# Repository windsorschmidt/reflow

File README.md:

# Reflow Oven Controller

_"Yeah man, but it's a **dry** heat!."_ —PFC William L. Hudson

## About

Hardware and firmware sources for a 2-channel reflow (toaster) oven controller.

In spite of great alternatives such as [Controleo3](http://www.whizoo.com/controleo3), I decided to build my own controller for personal use. The design is intended to be simple and self-contained. Comments and pull requests are welcome!

Some pictures of the assembled controller and completed oven retrofit [are online here](https://imgur.com/gallery/L4Zu2G3).

|  |  |

## Hardware Features

- Two triac-controlled power outputs (no external SSRs needed)
- AC line zero-crossing detection for reduced switching noise
- Temperature sensor using MAX31855 K-type thermocouple amplifier
- Compact user interface with OLED display and Cherry MX key-switches
- Data-logging output though USB and serial-to-Bluetooth module
- Tone transducer for audible alerts (e.g. reflow cycle complete)
- Mounts in a dedicated enclosure for simple wiring using IEC connectors
- [Aliens](https://en.wikipedia.org/wiki/Aliens_(film)) film inspired aesthetics

## Firmware Features

- Non-profiling PID routine controls triac outputs to track the active reflow profile
- Reflow profile can be viewed & edited at run-time (currently no ability to save edits)

## References

- [This project](https://www.allaboutcircuits.com/projects/controlling-ac-mains-with-a-microcontroller-for-fun-and-profit) was used as a basis for the triac control and zero-crossing detection circuitry
- [This Reddit user](https://www.reddit.com/user/rich-creamery-butter) provided [Assembly pics](https://imgur.com/a/sCKgO) used as a guide when converting my own oven
- The excellent [u8g2](https://github.com/olikraus/u8g2) library used to render user-interface graphics and text
- [Yusuke Kamiyamane](mailto:p@yusukekamiyamane.com)'s Tempesta Seven font used in the gnuplot script
- [KiCad](http://kicad-pcb.org/) EDA suite used for hardware schematic capture and PCB layout

## Disclaimer

This information is supplied "as is" and without warranties of any kind, express, implied, or statutory including, but not limited to, any implied warranty of merchantability, noninfringement or fitness for a particular purpose and no responsibility is assumed by the author for its use, nor for any infringements of patents or other rights of third parties that may result from its use.

In no event will the author be liable for any loss or damage including without limitation, indirect or consequential loss or damage, or any loss or damage whatsoever arising from or in connection with the use of this information.

## License

[MIT license](LICENSE)

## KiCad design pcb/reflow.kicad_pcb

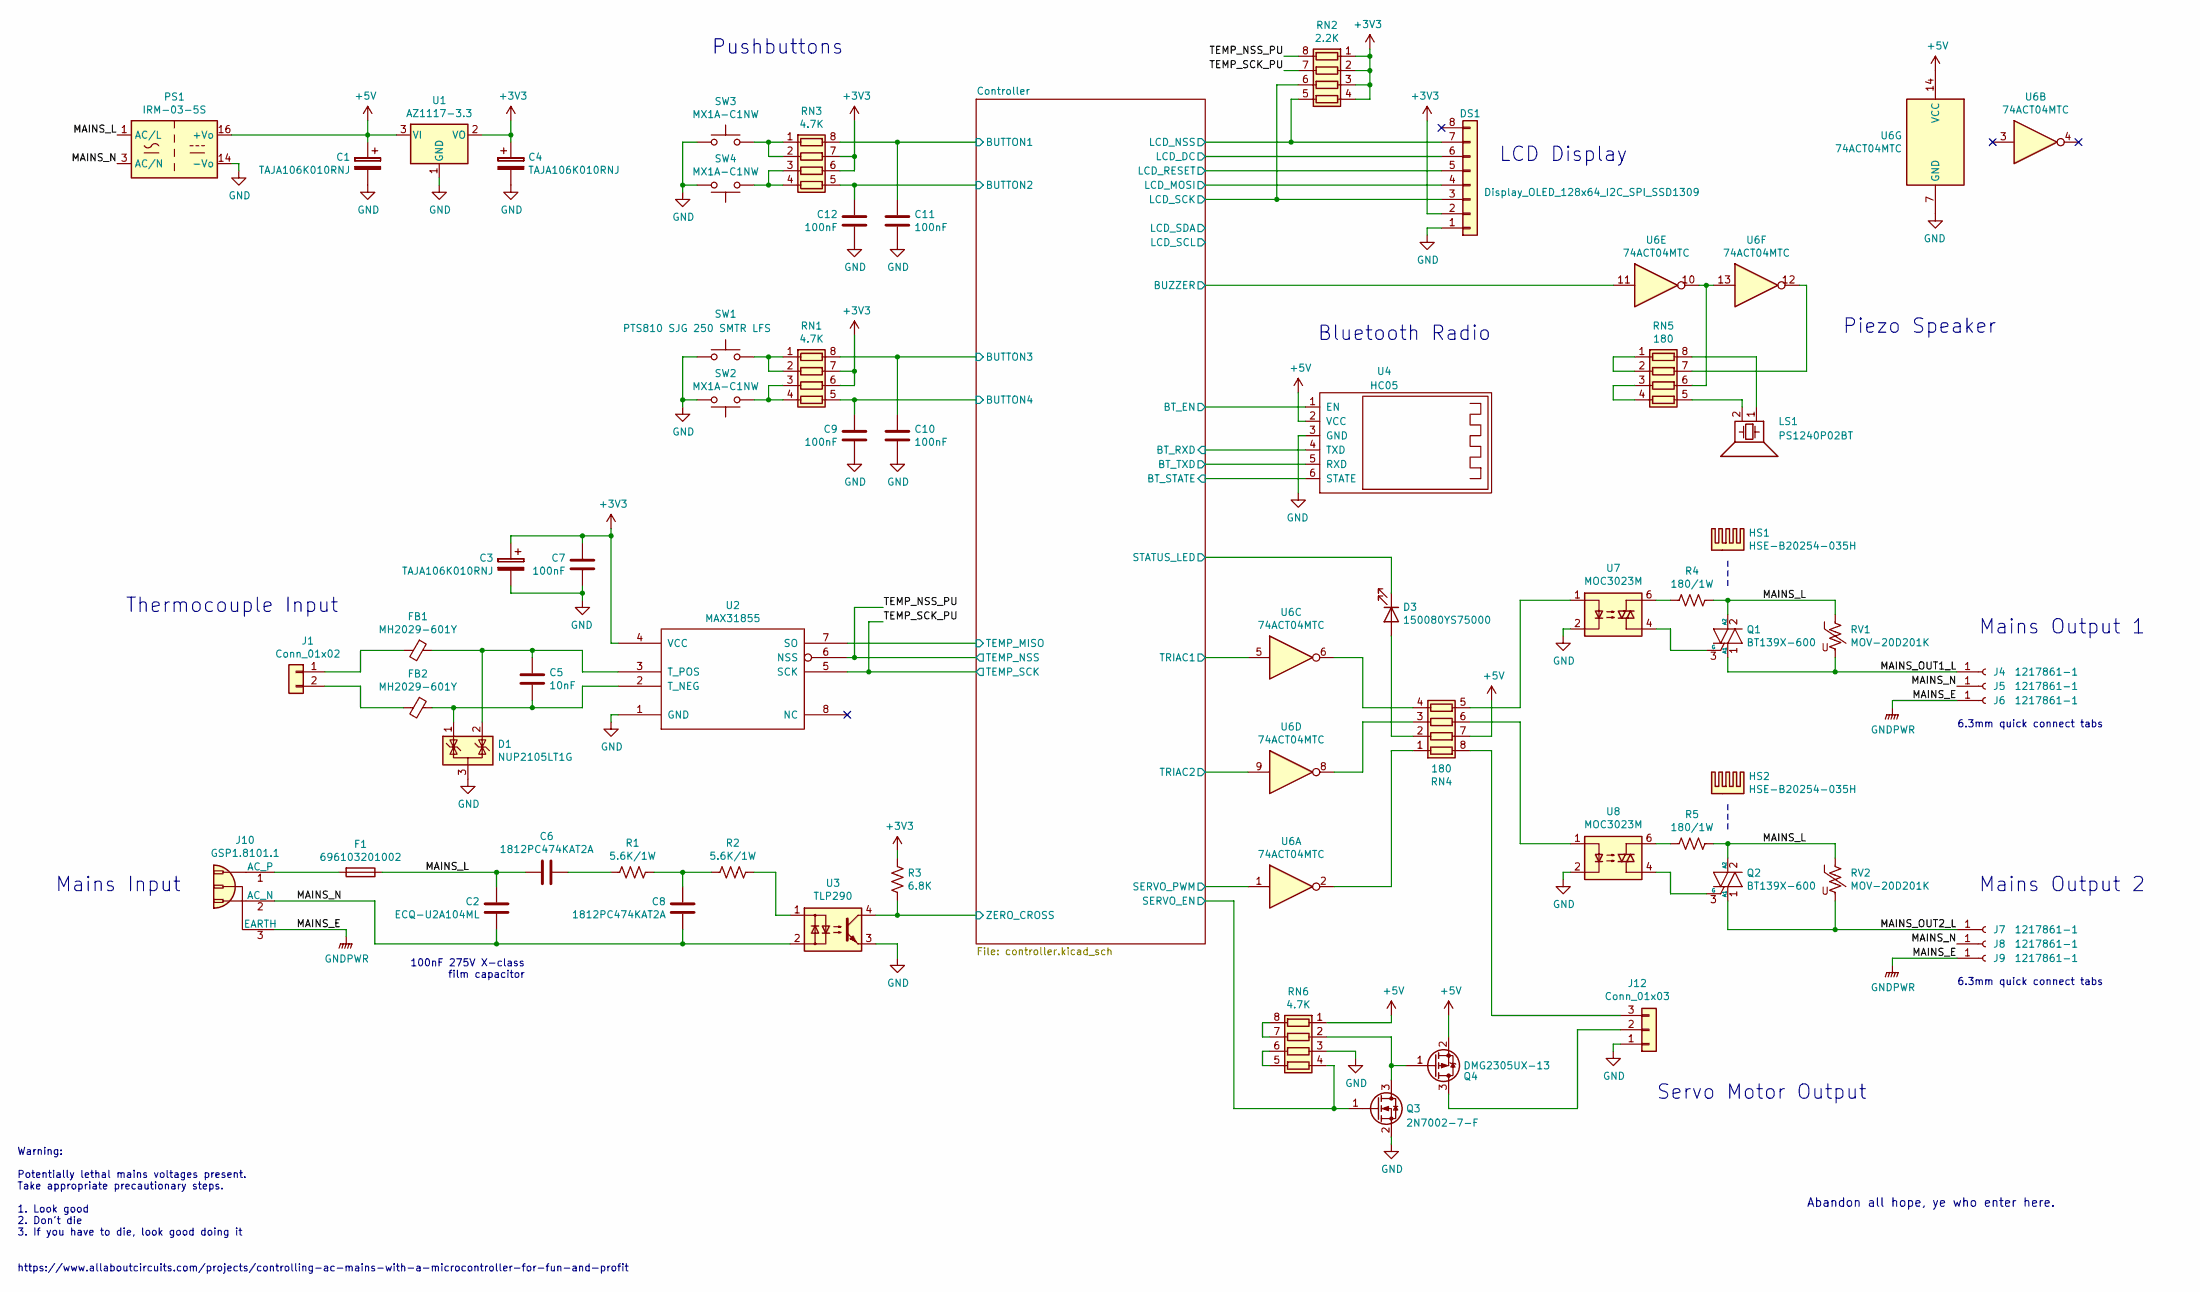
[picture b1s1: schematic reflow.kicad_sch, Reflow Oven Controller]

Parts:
C1, C3, C4: TAJA106K010RNJ; CP_EIA-3216-18_Kemet-A
C2: ECQ-U2A104ML; C_Rect_L18.0mm_W6.0mm_P15.00mm_FKS3_FKP3
C5: 10nF; C_0805_2012Metric
C6, C8: 1812PC474KAT2A; C_1812_4532Metric
C7, C9, C10, C11, C12: 100nF; C_0805_2012Metric
D1: NUP2105LT1G; SOT-23
D3: 150080YS75000; LED_0805_2012Metric
DS1: Display_OLED_128x64_I2C_SPI_SSD1309
F1: 696103201002; Fuseholder_Cylinder-5x20mm_Stelvio-Kontek_PTF78_Horizontal_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
FB1, FB2: MH2029-601Y; L_0805_2012Metric
HS1, HS2: HSE-B20254-035H; Heatsink_CUI_HSE-B20254-035H
J1: Conn_01x02; PinHeader_1x02_P2.54mm_Vertical
J4, J5, J6, J7, J8, J9: 1217861-1; Connector_FastOn_6.35mm
J10: GSP1.8101.1; Connector_Schurter_GSP1.8101.1
J12: Conn_01x03; PinHeader_1x03_P2.54mm_Vertical
LS1: PS1240P02BT; Buzzer_TDK_PS1240P02BT
PS1: IRM-03-5S; Converter_ACDC_MeanWell_IRM-03-xx_SMD
Q1, Q2: BT139X-600; TO-220-3_Vertical
Q3: 2N7002-7-F; SOT-23
Q4: DMG2305UX-13; SOT-23
R1, R2: 5.6K/1W; R_2512_6332Metric
R3: 6.8K; R_0805_2012Metric
R4, R5: 180/1W; R_2512_6332Metric
RN1, RN3, RN6: 4.7K; R_Array_Convex_4x0603
RN2: 2.2K; R_Array_Convex_4x0603
RN4, RN5: 180; R_Array_Convex_4x0603
RV1, RV2: MOV-20D201K; RV_Disc_D21.5mm_W4.3mm_P10mm
SW1: PTS810 SJG 250 SMTR LFS; Pushbutton_PTS810_SJx_250_SMTR_LFS
SW2, SW3, SW4: MX1A-C1NW; Switch_Cherry_MX1A_1.00u_PCB
U1: AZ1117-3.3; SOT-223
U2: MAX31855; SOIC-8_3.9x4.9mm_P1.27mm
U3: TLP290; SOP-4_4.4x2.8mm_P1.27mm
U4: HC05; Module_Bluetooth_HC05
U6: 74ACT04MTC; TSSOP-14_4.4x5mm_P0.65mm
U7, U8: MOC3023M; DIP-6_W7.62mm

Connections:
+3V3: C3.1, C4.1, C7.1, DS1.2, R3.2, RN1.6 (R3.2), RN1.7 (R2.2), RN2.1 (R1.1), RN2.2 (R2.1), RN2.3 (R3.1), RN2.4 (R4.1), RN3.6 (R3.2), RN3.7 (R2.2), U1.2 (VO), U2.4 (VCC); also elsewhere on the board
+5V: C1.1, PS1.16 (+Vo), Q4.2 (S), RN4.7 (R2.2), RN6.1 (R1.1), U1.3 (VI), U4.2 (VCC), U6.14 (VCC); also elsewhere on the board
/Controller/BT_EN: U4.1 (EN); also elsewhere on the board
/Controller/BT_RXD: U4.4 (TXD); also elsewhere on the board
/Controller/BT_STATE: U4.6 (STATE); also elsewhere on the board
/Controller/BT_TXD: U4.5 (RXD); also elsewhere on the board
/Controller/BUTTON1: C11.1, RN3.8 (R1.2); also elsewhere on the board
/Controller/BUTTON2: C12.2, RN3.5 (R4.2); also elsewhere on the board
/Controller/BUTTON3: C10.1, RN1.8 (R1.2); also elsewhere on the board
/Controller/BUTTON4: C9.2, RN1.5 (R4.2); also elsewhere on the board
/Controller/BUZZER: U6.11; also elsewhere on the board
/Controller/LCD_DC: DS1.6; also elsewhere on the board
/Controller/LCD_MOSI: DS1.4; also elsewhere on the board
/Controller/LCD_NSS: DS1.7, RN2.5 (R4.2); also elsewhere on the board
/Controller/LCD_RESET: DS1.5; also elsewhere on the board
/Controller/LCD_SCK: DS1.3, RN2.6 (R3.2); also elsewhere on the board
/Controller/SERVO_EN: Q3.1 (G), RN6.4 (R4.1); also elsewhere on the board
/Controller/SERVO_PWM: U6.1; also elsewhere on the board
/Controller/STATUS_LED: D3.1 (K); also elsewhere on the board
/Controller/TEMP_MISO: U2.7 (SO); also elsewhere on the board
/Controller/TRIAC1: U6.5; also elsewhere on the board
/Controller/TRIAC2: U6.9; also elsewhere on the board
/Controller/ZERO_CROSS: R3.1, U3.4; also elsewhere on the board
/MAINS_L: C2.1, C6.2, F1.1, PS1.1 (AC/L), Q1.2 (A2), Q2.2 (A2), R4.1, R5.1, RV1.1, RV2.1
/MAINS_N: C2.2, C8.1, J5.1, J8.1, J10.2 (AC_N), PS1.3 (AC/N), U3.2
/MAINS_OUT1_L: J4.1, Q1.1 (A1), RV1.2
/MAINS_OUT2_L: J7.1, Q2.1 (A1), RV2.2
/TEMP_NSS_PU: RN2.8 (R1.2), U2.6 (NSS); also elsewhere on the board
/TEMP_SCK_PU: RN2.7 (R2.2), U2.5 (SCK); also elsewhere on the board
GND: C1.2, C3.2, C4.2, C7.2, C9.1, C10.2, C11.2, C12.1, D1.3 (A), DS1.1, J12.1, PS1.14 (-Vo), Q3.2 (S), RN6.3 (R3.1), SW1.1, SW2.1, SW3.1, SW4.1, U1.1 (GND), U2.1 (GND), U3.3, U4.3 (GND), U6.7 (GND), U7.2, U8.2; also elsewhere on the board
GNDPWR: J6.1, J9.1, J10.3 (EARTH)
unnamed: C5.1, D1.2 (K), FB1.1, U2.3 (T_POS)
unnamed: C5.2, D1.1 (K), FB2.1, U2.2 (T_NEG)
unnamed: C6.1, R1.2
unnamed: C8.2, R1.1, R2.2
unnamed: D3.2 (A), RN4.2 (R2.1)
unnamed: F1.2, J10.1 (AC_P)
unnamed: FB1.2, J1.1
unnamed: FB2.2, J1.2
unnamed: J12.2, Q4.3 (D)
unnamed: J12.3, RN4.8 (R1.2)
unnamed: LS1.1, RN5.8 (R1.2)
unnamed: LS1.2, RN5.5 (R4.2)
unnamed: Q1.3 (G), U7.4
unnamed: Q2.3 (G), U8.4
unnamed: Q3.3 (D), Q4.1 (G), RN6.2 (R2.1)
unnamed: R2.1, U3.1
unnamed: R4.2, U7.6
unnamed: R5.2, U8.6
unnamed: RN1.1 (R1.1), RN1.2 (R2.1), SW1.2
unnamed: RN1.3 (R3.1), RN1.4 (R4.1), SW2.2
unnamed: RN3.1 (R1.1), RN3.2 (R2.1), SW3.2
unnamed: RN3.3 (R3.1), RN3.4 (R4.1), SW4.2
unnamed: RN4.1 (R1.1), U6.2
unnamed: RN4.3 (R3.1), U6.8
unnamed: RN4.4 (R4.1), U6.6
unnamed: RN4.5 (R4.2), U7.1
unnamed: RN4.6 (R3.2), U8.1
unnamed: RN5.1 (R1.1), RN5.2 (R2.1)
unnamed: RN5.3 (R3.1), RN5.4 (R4.1)
unnamed: RN5.6 (R3.2), U6.10, U6.13
unnamed: RN5.7 (R2.2), U6.12
unnamed: RN6.5 (R4.2), RN6.6 (R3.2)
unnamed: RN6.7 (R2.2), RN6.8 (R1.2)

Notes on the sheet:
6.3mm quick connect tabs
Pushbuttons
Bluetooth Radio
Mains Input
Abandon all hope, ye who enter here.
Mains Output 2
100nF 275V X-class film capacitor
Thermocouple Input
https://www.allaboutcircuits.com/projects/controlling-ac-mains-with-a-microcontroller-for-fun-and-profit
LCD Display
Warning: Potentially lethal mains voltages present. Take appropriate precautionary steps. 1. Look good 2. Don't die 3. If you have to die, look good doing it
Mains Output 1
Servo Motor Output
Piezo Speaker

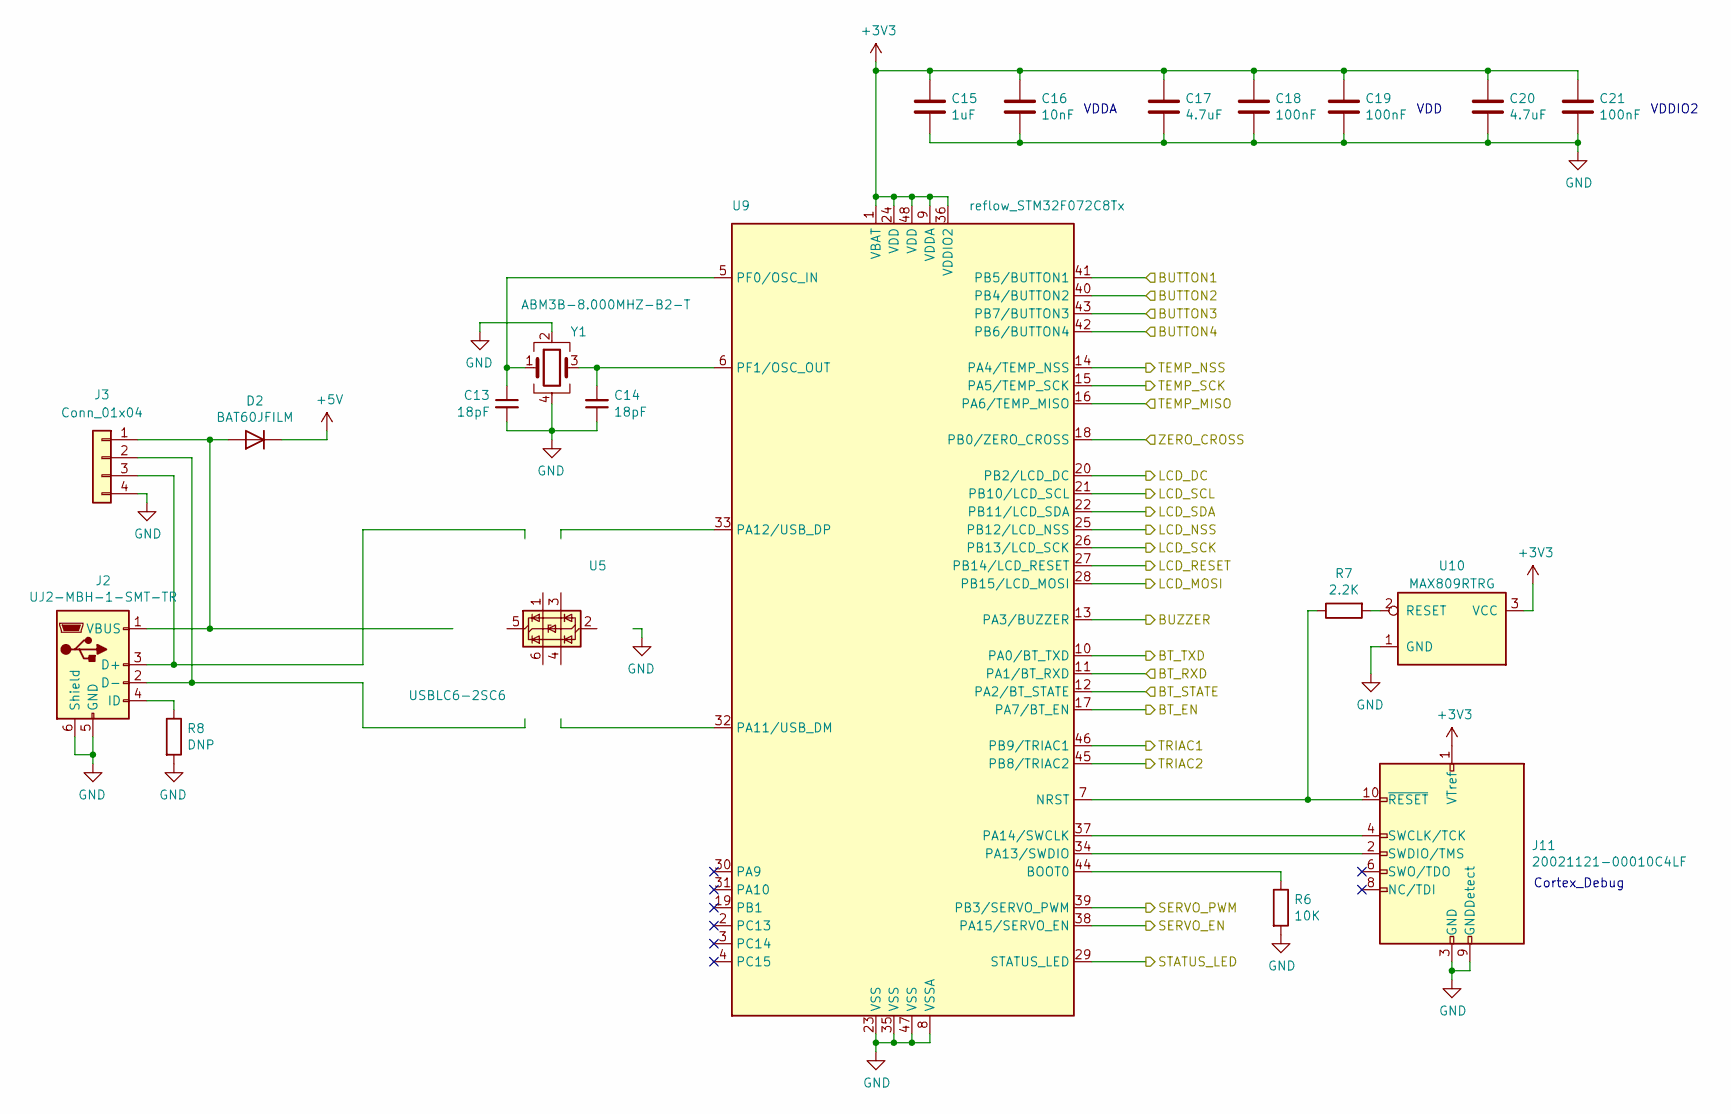
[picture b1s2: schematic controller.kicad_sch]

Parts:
C13, C14: 18pF; C_0603_1608Metric
C15: 1uF; C_0603_1608Metric
C16: 10nF; C_0603_1608Metric
C17, C20: 4.7uF; C_0805_2012Metric
C18, C19, C21: 100nF; C_0603_1608Metric
D2: BAT60JFILM; D_SOD-323
J2: UJ2-MBH-1-SMT-TR; USB_Mini-B_Lumberg_2486_01_Horizontal
J3: Conn_01x04; PinHeader_1x04_P2.54mm_Vertical
J11: 20021121-00010C4LF; PinHeader_2x05_P1.27mm_Vertical_SMD
R6: 10K; R_0603_1608Metric
R7: 2.2K; R_0603_1608Metric
R8: DNP; R_0603_1608Metric
U5: USBLC6-2SC6; SOT-23-6
U9: reflow_STM32F072C8Tx; LQFP-48_7x7mm_P0.5mm
U10: MAX809RTRG; SOT-23
Y1: ABM3B-8.000MHZ-B2-T; Crystal_Abracon_ABM3B-8.000MHZ-B2-T

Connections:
+3V3: C15.1, C16.2, C17.2, C18.1, C19.1, C20.2, C21.1, J11.1 (VTref), U9.1 (VBAT), U9.9 (VDDA), U9.24 (VDD), U9.36 (VDDIO2), U9.48 (VDD), U10.3 (VCC); also elsewhere on the board
+5V: D2.1 (K); also elsewhere on the board
/Controller/BT_EN: U9.17 (PA7/BT_EN); also elsewhere on the board
/Controller/BT_RXD: U9.11 (PA1/BT_RXD); also elsewhere on the board
/Controller/BT_STATE: U9.12 (PA2/BT_STATE); also elsewhere on the board
/Controller/BT_TXD: U9.10 (PA0/BT_TXD); also elsewhere on the board
/Controller/BUTTON1: U9.41 (PB5/BUTTON1); also elsewhere on the board
/Controller/BUTTON2: U9.40 (PB4/BUTTON2); also elsewhere on the board
/Controller/BUTTON3: U9.43 (PB7/BUTTON3); also elsewhere on the board
/Controller/BUTTON4: U9.42 (PB6/BUTTON4); also elsewhere on the board
/Controller/BUZZER: U9.13 (PA3/BUZZER); also elsewhere on the board
/Controller/LCD_DC: U9.20 (PB2/LCD_DC); also elsewhere on the board
/Controller/LCD_MOSI: U9.28 (PB15/LCD_MOSI); also elsewhere on the board
/Controller/LCD_NSS: U9.25 (PB12/LCD_NSS); also elsewhere on the board
/Controller/LCD_RESET: U9.27 (PB14/LCD_RESET); also elsewhere on the board
/Controller/LCD_SCK: U9.26 (PB13/LCD_SCK); also elsewhere on the board
/Controller/SERVO_EN: U9.38 (PA15/SERVO_EN); also elsewhere on the board
/Controller/SERVO_PWM: U9.39 (PB3/SERVO_PWM); also elsewhere on the board
/Controller/STATUS_LED: U9.29 (STATUS_LED); also elsewhere on the board
/Controller/TEMP_MISO: U9.16 (PA6/TEMP_MISO); also elsewhere on the board
/Controller/TRIAC1: U9.46 (PB9/TRIAC1); also elsewhere on the board
/Controller/TRIAC2: U9.45 (PB8/TRIAC2); also elsewhere on the board
/Controller/ZERO_CROSS: U9.18 (PB0/ZERO_CROSS); also elsewhere on the board
/TEMP_NSS_PU: U9.14 (PA4/TEMP_NSS); also elsewhere on the board
/TEMP_SCK_PU: U9.15 (PA5/TEMP_SCK); also elsewhere on the board
GND: C13.2, C14.1, C15.2, C16.1, C17.1, C18.2, C19.2, C20.1, C21.2, J2.5 (GND), J2.6 (Shield), J3.4, J11.3 (GND), J11.5 (GND), J11.9 (GNDDetect), R6.2, R8.2, U5.2 (GND), U9.8 (VSSA), U9.23 (VSS), U9.35 (VSS), U9.47 (VSS), U10.1 (GND), Y1.2, Y1.4; also elsewhere on the board
unnamed: C13.1, U9.5 (PF0/OSC_IN), Y1.1
unnamed: C14.2, U9.6 (PF1/OSC_OUT), Y1.3
unnamed: J2.4 (ID), R8.1
unnamed: J11.2 (SWDIO/TMS), U9.34 (PA13/SWDIO)
unnamed: J11.4 (SWCLK/TCK), U9.37 (PA14/SWCLK)
unnamed: J11.10 (~RESET), R7.1, U9.7 (NRST)
unnamed: R6.1, U9.44 (BOOT0)
unnamed: R7.2, U10.2 (RESET)
unnamed: U5.1 (I/O1), U9.33 (PA12/USB_DP)
unnamed: U5.3 (I/O2), U9.32 (PA11/USB_DM)

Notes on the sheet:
VDDIO2
VDD
VDDA
Cortex_Debug

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
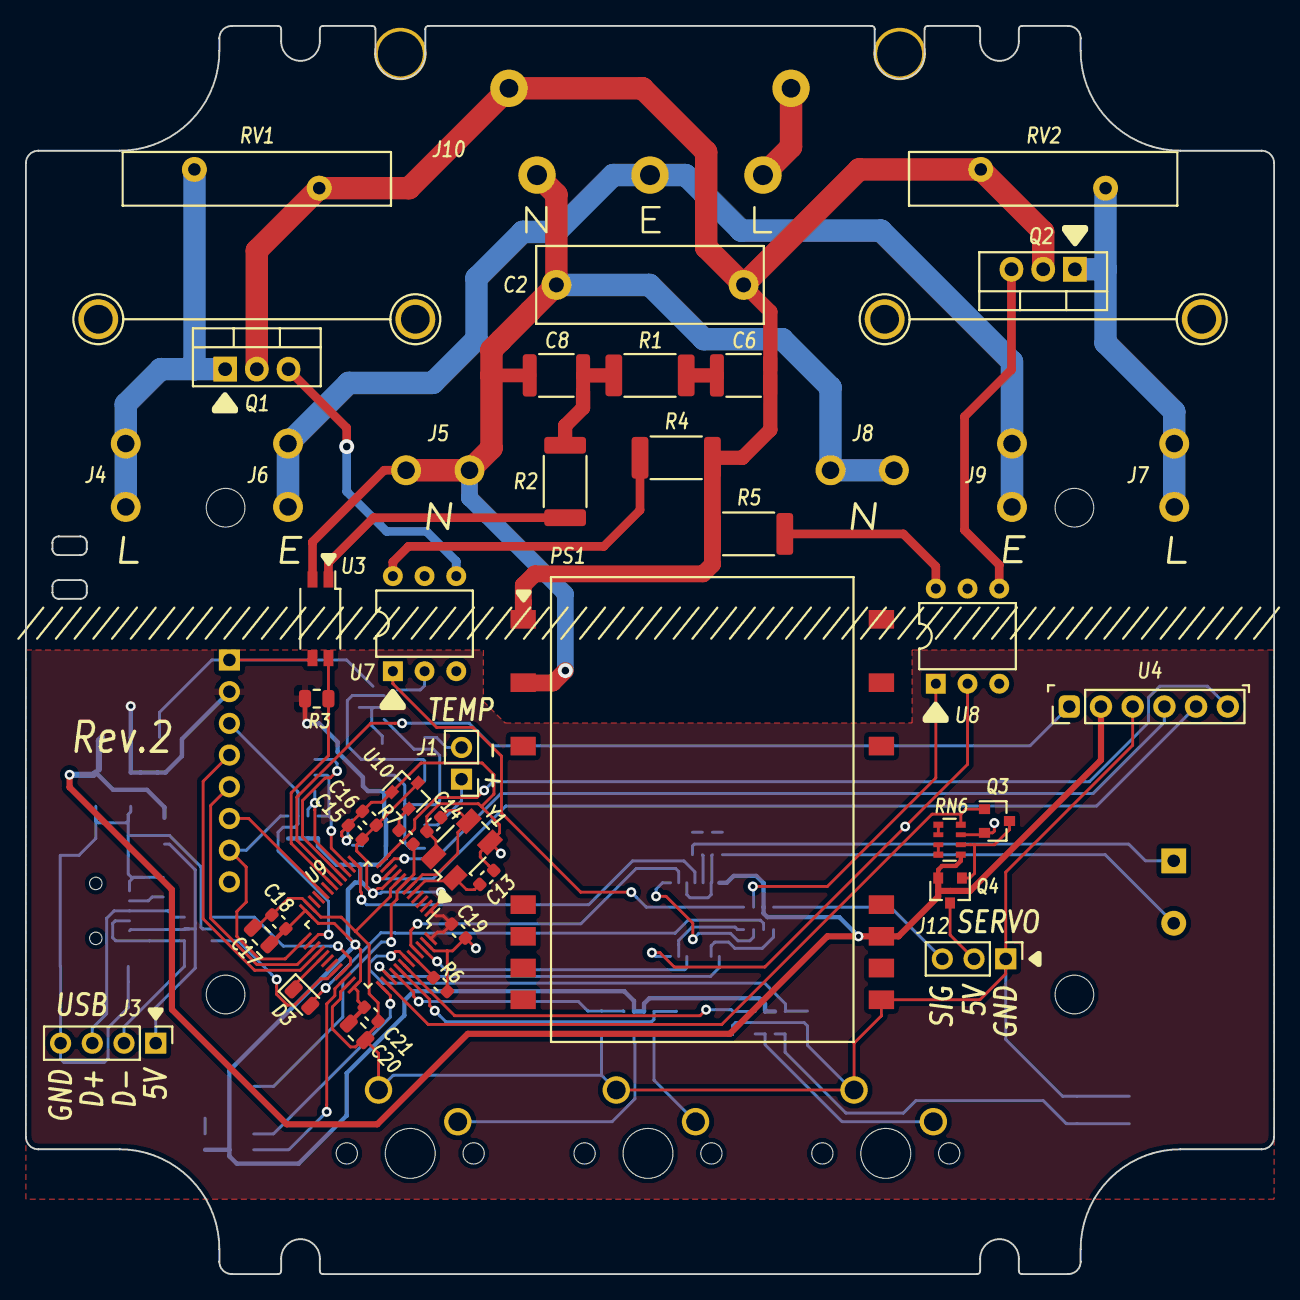
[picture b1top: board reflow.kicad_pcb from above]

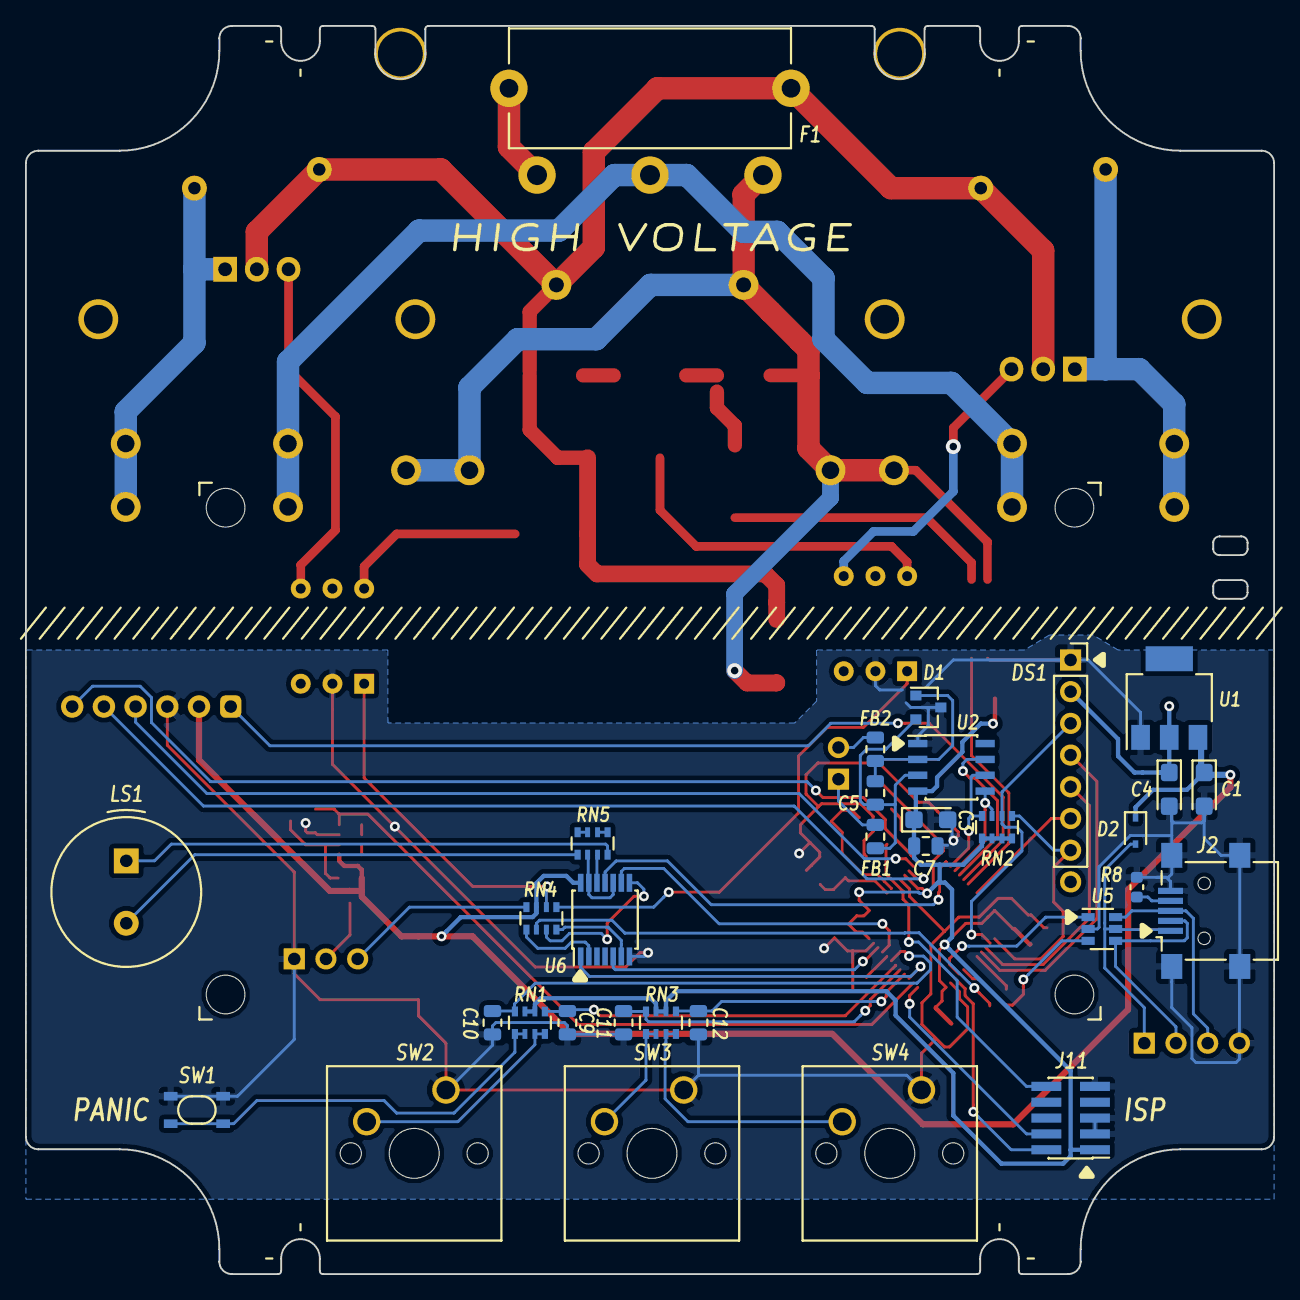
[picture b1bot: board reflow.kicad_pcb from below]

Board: 2 copper layers, 100.0 x 100.0 mm, 95 parts (38 on the bottom side), 77 nets.

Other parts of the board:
G1, G2, G4, G5: Artwork_Pin_Marker
G3, G6, G7, G8, G9, G10, G11, G12, G13, G14, G15: Artwork_Pin_Marker_Small
MNT**: Mount_Zip_Tie; MOUNT_ZIP_TIE_2X

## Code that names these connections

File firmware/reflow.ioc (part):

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Mcu.Name=STM32F072C(8-B)Tx
Mcu.Package=LQFP48
Mcu.UserName=STM32F072C8Tx
PA0.Mode=Asynchronous
PA0.Signal=USART4_TX
PA1.Mode=Asynchronous
PA1.Signal=USART4_RX
PA11.Mode=Device
PA11.Signal=USB_DM
PA12.Mode=Device
PA12.Signal=USB_DP
PA13.GPIOParameters=GPIO_Label
PA13.GPIO_Label=SWDIO
PA13.Mode=Serial_Wire
PA13.Signal=SYS_SWDIO
PA14.GPIOParameters=GPIO_Label
PA14.GPIO_Label=SWCLK
PA14.Mode=Serial_Wire
PA14.Signal=SYS_SWCLK
PA15.GPIOParameters=GPIO_Speed,PinState,GPIO_PuPd,GPIO_Label
PA15.GPIO_Label=SERVO_EN
PA15.GPIO_PuPd=GPIO_PULLDOWN
PA15.GPIO_Speed=GPIO_SPEED_FREQ_LOW
PA15.PinState=GPIO_PIN_RESET
PA15.Signal=GPIO_Output
PA2.GPIOParameters=GPIO_PuPd,GPIO_Label,GPIO_ModeDefaultEXTI
PA2.GPIO_Label=BT_STATE
PA2.GPIO_ModeDefaultEXTI=GPIO_MODE_IT_RISING_FALLING
PA2.GPIO_PuPd=GPIO_PULLUP
PA2.Signal=GPXTI2
PA3.GPIOParameters=GPIO_Label
PA3.GPIO_Label=BUZZER
PA3.Signal=S_TIM15_CH2
PA4.GPIOParameters=GPIO_Label
PA4.GPIO_Label=TEMP_NSS
PA4.Mode=NSS_Signal_Hard_Output
PA4.Signal=SPI1_NSS
PA5.GPIOParameters=GPIO_Label
PA5.GPIO_Label=TEMP_SCK
PA5.Mode=RX_Only_Simplex_Unidirect_Master
PA5.Signal=SPI1_SCK
PA6.GPIOParameters=GPIO_Label
PA6.GPIO_Label=TEMP_MISO
PA6.Mode=RX_Only_Simplex_Unidirect_Master
PA6.Signal=SPI1_MISO
PA7.GPIOParameters=GPIO_Speed,PinState,GPIO_PuPd,GPIO_Label
PA7.GPIO_Label=BT_EN
PA7.GPIO_PuPd=GPIO_PULLDOWN
PA7.GPIO_Speed=GPIO_SPEED_FREQ_HIGH
PA7.PinState=GPIO_PIN_RESET
PA7.Signal=GPIO_Output
PA8.GPIOParameters=GPIO_Speed,GPIO_Label,GPIO_ModeDefaultOutputPP
PA8.GPIO_Label=STATUS_LED
PA8.GPIO_ModeDefaultOutputPP=GPIO_MODE_OUTPUT_OD
PA8.GPIO_Speed=GPIO_SPEED_FREQ_HIGH
PA8.Signal=GPIO_Output
PB0.GPIOParameters=GPIO_PuPd,GPIO_Label,GPIO_ModeDefaultEXTI
PB0.GPIO_Label=ZERO_CROSS
PB0.GPIO_ModeDefaultEXTI=GPIO_MODE_IT_FALLING
PB0.GPIO_PuPd=GPIO_PULLUP
PB0.Signal=GPXTI0
PB12.GPIOParameters=GPIO_PuPd,GPIO_Label
PB12.GPIO_Label=OLED_NSS
PB12.GPIO_PuPd=GPIO_PULLUP
PB12.Mode=NSS_Signal_Hard_Output
PB12.Signal=SPI2_NSS
PB13.GPIOParameters=GPIO_PuPd,GPIO_Label
PB13.GPIO_Label=OLED_SCK
PB13.GPIO_PuPd=GPIO_PULLUP
PB13.Mode=TX_Only_Simplex_Unidirect_Master
PB13.Signal=SPI2_SCK
PB14.GPIOParameters=GPIO_Speed,PinState,GPIO_PuPd,GPIO_Label
PB14.GPIO_Label=OLED_RESET
PB14.GPIO_PuPd=GPIO_PULLUP
PB14.GPIO_Speed=GPIO_SPEED_FREQ_HIGH
PB14.PinState=GPIO_PIN_SET
PB14.Signal=GPIO_Output
PB15.GPIOParameters=GPIO_PuPd,GPIO_Label
PB15.GPIO_Label=OLED_MOSI
PB15.GPIO_PuPd=GPIO_PULLUP
PB15.Mode=TX_Only_Simplex_Unidirect_Master
PB15.Signal=SPI2_MOSI
PB2.GPIOParameters=GPIO_Speed,PinState,GPIO_PuPd,GPIO_Label
PB2.GPIO_Label=OLED_DC
PB2.GPIO_PuPd=GPIO_PULLUP
PB2.GPIO_Speed=GPIO_SPEED_FREQ_HIGH
PB2.PinState=GPIO_PIN_SET
PB2.Signal=GPIO_Output
PB3.GPIOParameters=PinState,GPIO_PuPd,GPIO_Label
PB3.GPIO_Label=FAN_TACH
PB3.GPIO_PuPd=GPIO_PULLUP
PB3.PinState=GPIO_PIN_SET
PB3.Signal=GPIO_Output
PB4.GPIOParameters=GPIO_PuPd,GPIO_Label,GPIO_ModeDefaultEXTI
PB4.GPIO_Label=BUTTON_NEXT
PB4.GPIO_ModeDefaultEXTI=GPIO_MODE_IT_FALLING
PB4.GPIO_PuPd=GPIO_PULLUP
PB4.Signal=GPXTI4
PB5.GPIOParameters=GPIO_PuPd,GPIO_Label,GPIO_ModeDefaultEXTI
PB5.GPIO_Label=BUTTON_SET
PB5.GPIO_ModeDefaultEXTI=GPIO_MODE_IT_FALLING
PB5.GPIO_PuPd=GPIO_PULLUP
PB5.Signal=GPXTI5
PB6.GPIOParameters=GPIO_PuPd,GPIO_Label,GPIO_ModeDefaultEXTI
PB6.GPIO_Label=BUTTON_PREV
PB6.GPIO_ModeDefaultEXTI=GPIO_MODE_IT_FALLING
PB6.GPIO_PuPd=GPIO_PULLUP
PB6.Signal=GPXTI6
PB7.GPIOParameters=GPIO_PuPd,GPIO_Label,GPIO_ModeDefaultEXTI
PB7.GPIO_Label=BUTTON_PANIC
PB7.GPIO_ModeDefaultEXTI=GPIO_MODE_IT_FALLING
PB7.GPIO_PuPd=GPIO_PULLUP
PB7.Signal=GPXTI7
PB8.GPIOParameters=GPIO_Speed,GPIO_Label
PB8.GPIO_Label=TRIAC2
PB8.GPIO_Speed=GPIO_SPEED_FREQ_HIGH
PB8.Signal=S_TIM16_CH1
PB9.GPIOParameters=GPIO_Speed,GPIO_Label
PB9.GPIO_Label=TRIAC1
PB9.GPIO_Speed=GPIO_SPEED_FREQ_HIGH
PB9.Signal=S_TIM17_CH1
PF0-OSC_IN.Mode=HSE-External-Oscillator
PF0-OSC_IN.Signal=RCC_OSC_IN
PF1-OSC_OUT.Mode=HSE-External-Oscillator
PF1-OSC_OUT.Signal=RCC_OSC_OUT
RCC.SYSCLKFreq_VALUE=48000000
RCC.SYSCLKSource=RCC_SYSCLKSOURCE_PLLCLK
board=custom

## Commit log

2019-02-15 move user interface mockup in to firmware directory
2019-02-15 add readme for plot script
2019-02-15 add link to oven and PCB images
2024-04-23 update pcb image
2024-04-23 misc edits
2025-08-05 update pcb for kicad 9
2025-08-05 use org file for readme
2025-08-20 remove pcb images
